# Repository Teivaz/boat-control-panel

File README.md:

# Panel 01

Electrical control panel for a boat. A single three-board unit that drives the
cabin relays, exposes them through a button panel with per-button RGB
feedback, and displays system state (battery, fuel and fresh-water level,
sensors, clock, nav-light selection) on a small OLED.

## Hardware layout

Three PIC18F27Q84 boards communicate over a shared I2C bus (multi-master):

| Board | Directory | Role |
|---|---|---|
| Switching | `circuit/board1-switching/` | 16 relay outputs (shift-register + mux back-read), 2 float-meter inputs, battery divider, 3 digital sensors (bilge / shore / AC). |
| Button (L/R) | `circuit/board2-buttons/` | 7 momentary buttons with per-button RGB indicator LEDs and configurable trigger modes. Two physical boards per unit (left and right), address selected by strap. |
| Main | `circuit/board3-main/` | SSD1322 OLED, DS3231 RTC, config switch. Orchestrates the other boards: receives button events, maintains relay intent, drives nav-light logic, and hosts the config menu. |

## Repository layout

- `firmware/` — C firmware for all three boards. Self-contained build via
  Docker (`firmware/build.sh`). See [`firmware/CLAUDE.md`](firmware/CLAUDE.md)
  and [`firmware/protocol.md`](firmware/protocol.md) for the I2C protocol,
  module conventions, and per-board details.
- `circuit/` — KiCad schematics and PCB layouts, one directory per board plus
  a shared symbol/footprint library (`panel-library.*`) and connection
  diagrams.
- `design/` — Front-panel artwork (Affinity Designer / Photo sources) and DXF
  exports for panel cutouts.
- `models/` — STEP files for mechanical assemblies and 3D-printed parts.
- `playground/` — Experimental sketches (currently the SSD1322 I2C display
  bring-up).

## Functional overview

- **Power**: a panel-wide power button on the left board gates every
  non-nav-light relay. Relay and nav-mode state are restored from a RAM
  snapshot when power is toggled back on.
- **Relays (5..15)**: instruments, autopilot, inverter, water pump, fridge,
  deck/cabin lights, USB, two aux channels. Each is tied to a single button
  and toggles on press. A button flags ERROR when the physical relay state
  doesn't converge to the requested one.
- **Nav lights (relays 0..4)**: anchoring / tricolor / steaming / bow / stern
  driven by a 3-button nav-mode selector. The main board filters requested
  combinations against the configured "enabled lights" mask (set in the
  config menu) and surfaces an error if the request is incompatible.
- **Config mode**: toggling the RA7 switch on the main board enters a menu
  (nav-light mask, time-of-day, water/fuel float offsets). The same buttons
  become menu navigation while active.
- **Button trigger modes**: each button has an independent trigger
  (release / hold / change) and time threshold, configured via the protocol
  and persisted to each board's data EEPROM.

## Firmware highlights

- No RTOS — all boards share a cooperative 1 ms-tick scheduler (`libcomm/
  task.c`) with a deferred ISR-to-main-loop queue (`run_in_main_loop`).
- Transport-agnostic protocol library (`libcomm/`) linked into all three
  boards. I2C, buttons, relays, NVM, and display code are board-local.
- Built with Microchip XC8 v3.10 inside a pinned Docker image; no MPLAB X
  install required. `./firmware/build.sh` from a board source directory
  produces a `.hex` in `dist/default/production/`.
- No unit tests — validation is done on hardware via a PICkit/ICD
  programmer. Per-board readmes in `firmware/board{1,3}/readme.md` document
  pinout and wiring.

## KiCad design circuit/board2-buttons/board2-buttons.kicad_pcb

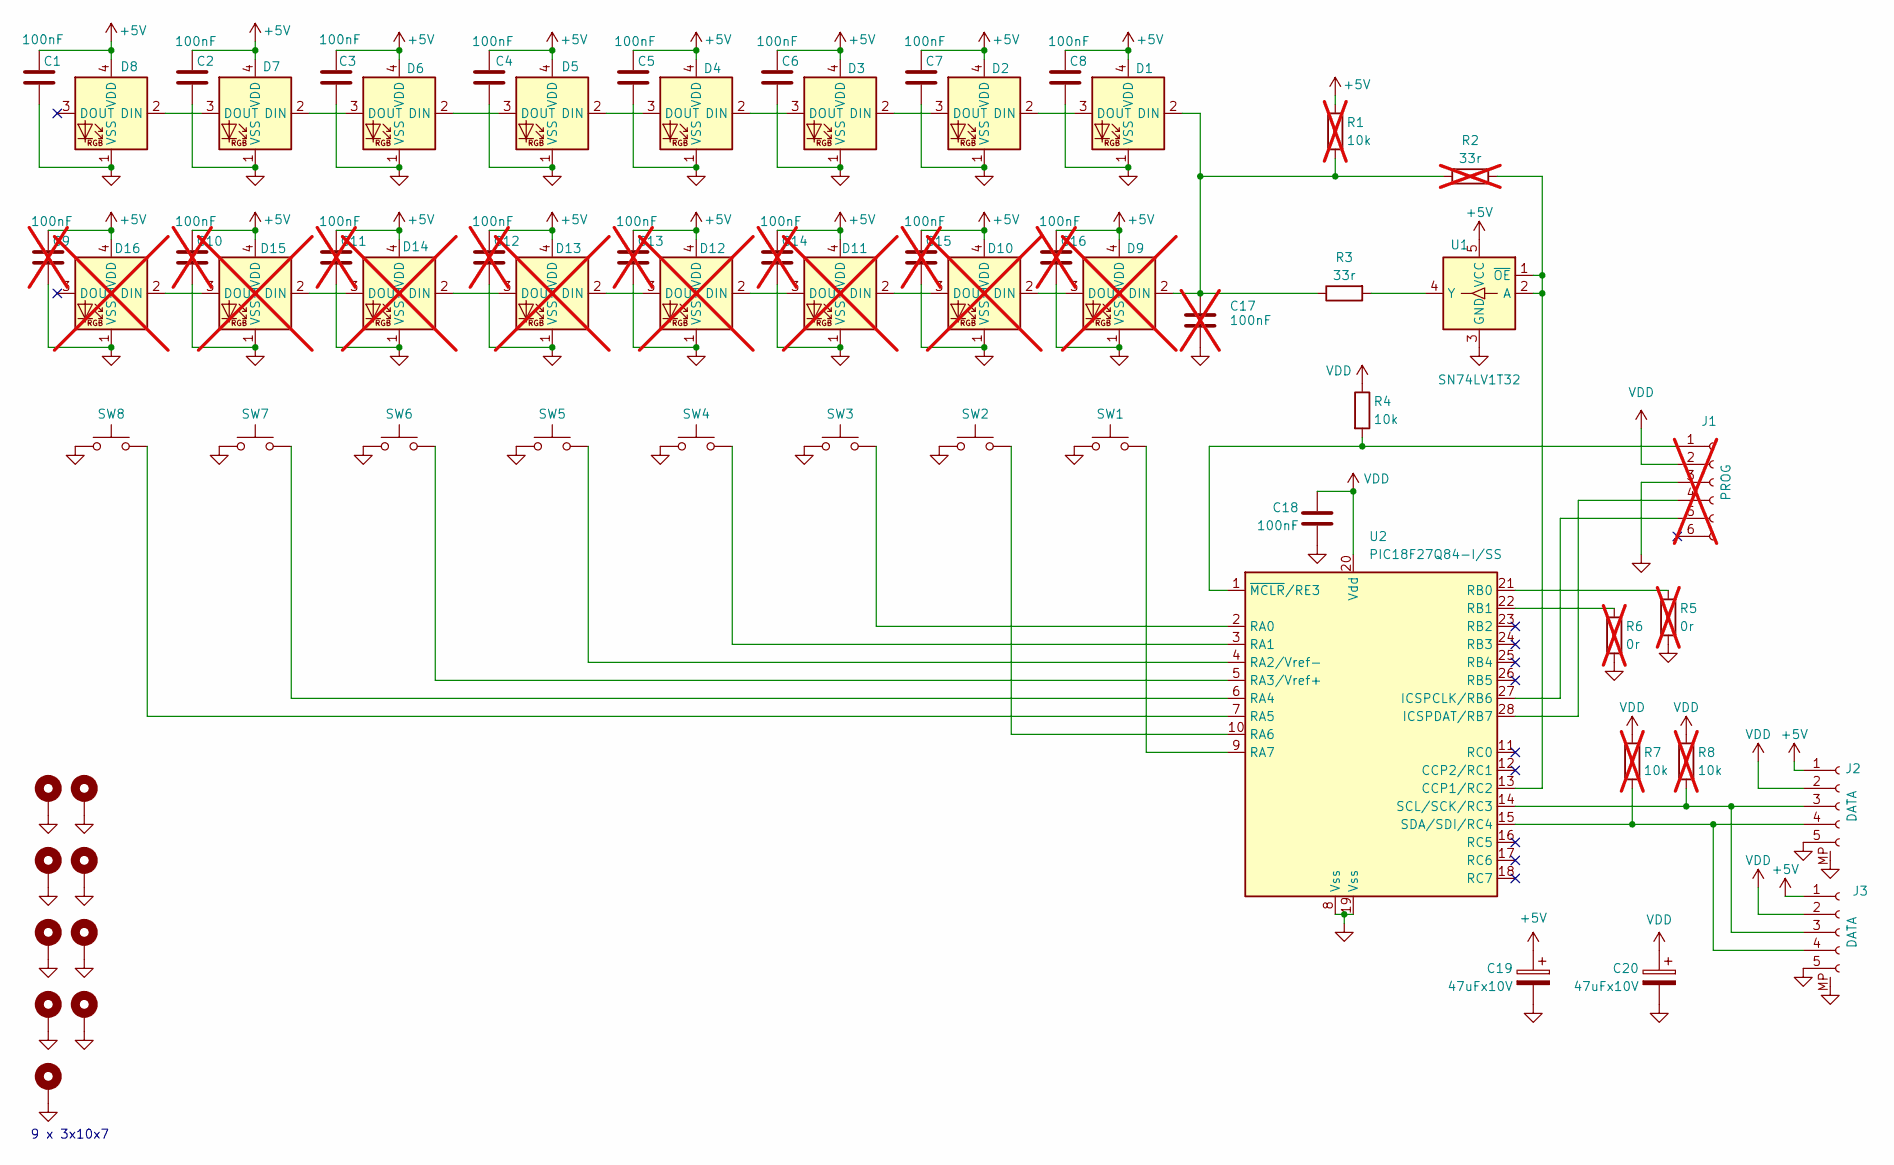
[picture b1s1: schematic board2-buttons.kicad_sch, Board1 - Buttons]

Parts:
C1, C2, C3, C4, C5, C6, C7, C8, C18: 100nF; C_0805_2012Metric_Pad1.18x1.45mm_HandSolder
C9, C10, C11, C12, C13, C14, C15, C16, C17: 100nF; C_0805_2012Metric_Pad1.18x1.45mm_HandSolder; not fitted
C19, C20: 47uFx10V; CP_EIA-3528-12_Kemet-T_HandSolder
D1, D2, D3, D4, D5, D6, D7, D8: LiteOn_LTST-E563C; LED_LiteOn_LTST-E563C_PLCC4_5.0x5.0mm_P3.2mm
D9, D10, D11, D12, D13, D14, D15, D16: LiteOn_LTST-E563C; LED_LiteOn_LTST-E563C_PLCC4_5.0x5.0mm_P3.2mm; not fitted
H1, H2, H3, H4, H5, H6, H7, H8, H9: 3X10X7; MountingHole_3.2mm_M3_Pad_Via_oval
J1: 1x5x2.54; PinHeader_1x06_P2.54mm_Vertical; not fitted
J2, J3: PicoLock; Molex_Pico-Lock_504050-0591_1x05-1MP_P1.50mm_Horizontal
R1, R7, R8: 10k; R_0805_2012Metric_Pad1.20x1.40mm_HandSolder; not fitted
R2: 33r; R_0805_2012Metric_Pad1.20x1.40mm_HandSolder; not fitted
R3: 33r; R_0805_2012Metric_Pad1.20x1.40mm_HandSolder
R4: 10k; R_0805_2012Metric_Pad1.20x1.40mm_HandSolder
R5, R6: 0r; R_0805_2012Metric_Pad1.20x1.40mm_HandSolder; not fitted
SW1, SW2, SW3, SW4, SW5, SW6, SW7, SW8: EVPCD; ButtonSMT_Panasonic_EVPCD
U1: SN74LV1T32; SOT-23-5
U2: PIC18F27Q84-I/SS; SSOP-28-5.3mm

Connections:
+5V: C1.1, C2.1, C3.1, C4.1, C5.1, C6.1, C7.1, C8.1, C9.1, C10.1, C11.1, C12.1, C13.1, C14.1, C15.1, C16.1, C19.1, D1.4 (VDD), D2.4 (VDD), D3.4 (VDD), D4.4 (VDD), D5.4 (VDD), D6.4 (VDD), D7.4 (VDD), D8.4 (VDD), D9.4 (VDD), D10.4 (VDD), D11.4 (VDD), D12.4 (VDD), D13.4 (VDD), D14.4 (VDD), D15.4 (VDD), D16.4 (VDD), J2.1, J3.1, R1.1, U1.5 (VCC)
GND: C1.2, C2.2, C3.2, C4.2, C5.2, C6.2, C7.2, C8.2, C9.2, C10.2, C11.2, C12.2, C13.2, C14.2, C15.2, C16.2, C17.1, C18.2, C19.2, C20.2, D1.1 (VSS), D2.1 (VSS), D3.1 (VSS), D4.1 (VSS), D5.1 (VSS), D6.1 (VSS), D7.1 (VSS), D8.1 (VSS), D9.1 (VSS), D10.1 (VSS), D11.1 (VSS), D12.1 (VSS), D13.1 (VSS), D14.1 (VSS), D15.1 (VSS), D16.1 (VSS), H1.1, H2.1, H3.1, H4.1, H5.1, H6.1, H7.1, H8.1, H9.1, J1.3, J2.5, J2.MP, J3.5, J3.MP, R5.1, R6.2, SW1.1, SW2.1, SW3.1, SW4.1, SW5.1, SW6.1, SW7.1, SW8.1, U1.3 (GND), U2.8 (Vss), U2.19 (Vss)
unnamed: C17.2, D1.2 (DIN), D9.2 (DIN), R1.2, R2.2, R3.1
unnamed: D1.3 (DOUT), D2.2 (DIN)
unnamed: D2.3 (DOUT), D3.2 (DIN)
unnamed: D3.3 (DOUT), D4.2 (DIN)
unnamed: D4.3 (DOUT), D5.2 (DIN)
unnamed: D5.3 (DOUT), D6.2 (DIN)
unnamed: D6.3 (DOUT), D7.2 (DIN)
unnamed: D7.3 (DOUT), D8.2 (DIN)
unnamed: D9.3 (DOUT), D10.2 (DIN)
unnamed: D10.3 (DOUT), D11.2 (DIN)
unnamed: D11.3 (DOUT), D12.2 (DIN)
unnamed: D12.3 (DOUT), D13.2 (DIN)
unnamed: D13.3 (DOUT), D14.2 (DIN)
unnamed: D14.3 (DOUT), D15.2 (DIN)
unnamed: D15.3 (DOUT), D16.2 (DIN)
unnamed: J1.1, R4.2, U2.1 (~MCLR/RE3)
unnamed: J1.4, U2.28 (ICSPDAT/RB7)
unnamed: J1.5, U2.27 (ICSPCLK/RB6)
unnamed: J2.3, J3.3, R8.2, U2.14 (SCL/SCK/RC3)
unnamed: J2.4, J3.4, R7.2, U2.15 (SDA/SDI/RC4)
unnamed: R2.1, U1.1 (~OE), U1.2 (A), U2.13 (CCP1/RC2)
unnamed: R3.2, U1.4 (Y)
unnamed: SW3.2, U2.2 (RA0)
unnamed: SW4.2, U2.3 (RA1)
unnamed: SW5.2, U2.4 (RA2/Vref-)
unnamed: SW6.2, U2.5 (RA3/Vref+)
unnamed: SW7.2, U2.6 (RA4)
unnamed: SW8.2, U2.7 (RA5)
unnamed: SW2.2, U2.10 (RA6)
unnamed: SW1.2, U2.9 (RA7)
unnamed: R5.2, U2.21 (RB0)
unnamed: R6.1, U2.22 (RB1)
VDD: C18.1, C20.1, J1.2, J2.2, J3.2, R4.1, R7.1, R8.1, U2.20 (Vdd)

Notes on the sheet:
9 x 3x10x7

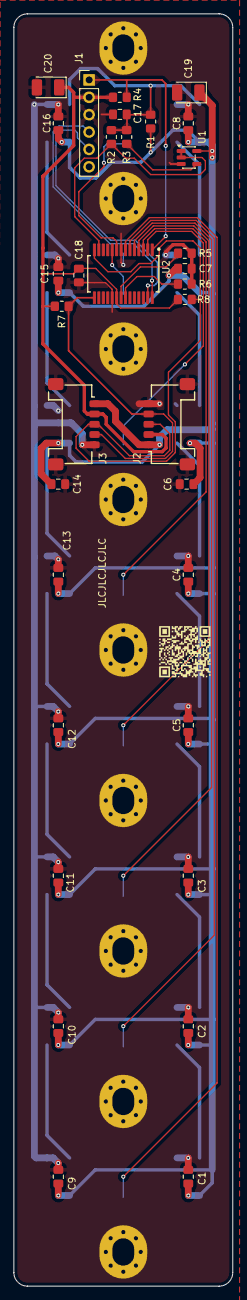
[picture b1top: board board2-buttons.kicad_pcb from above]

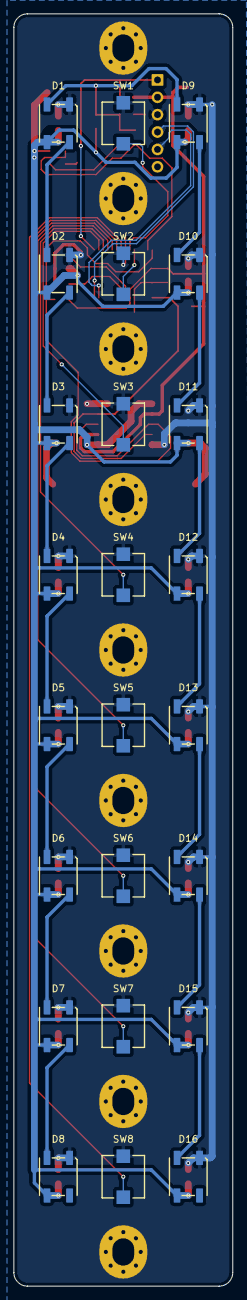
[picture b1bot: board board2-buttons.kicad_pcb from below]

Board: 2 copper layers, 32.0 x 186.0 mm, 66 parts (24 on the bottom side), 35 nets.

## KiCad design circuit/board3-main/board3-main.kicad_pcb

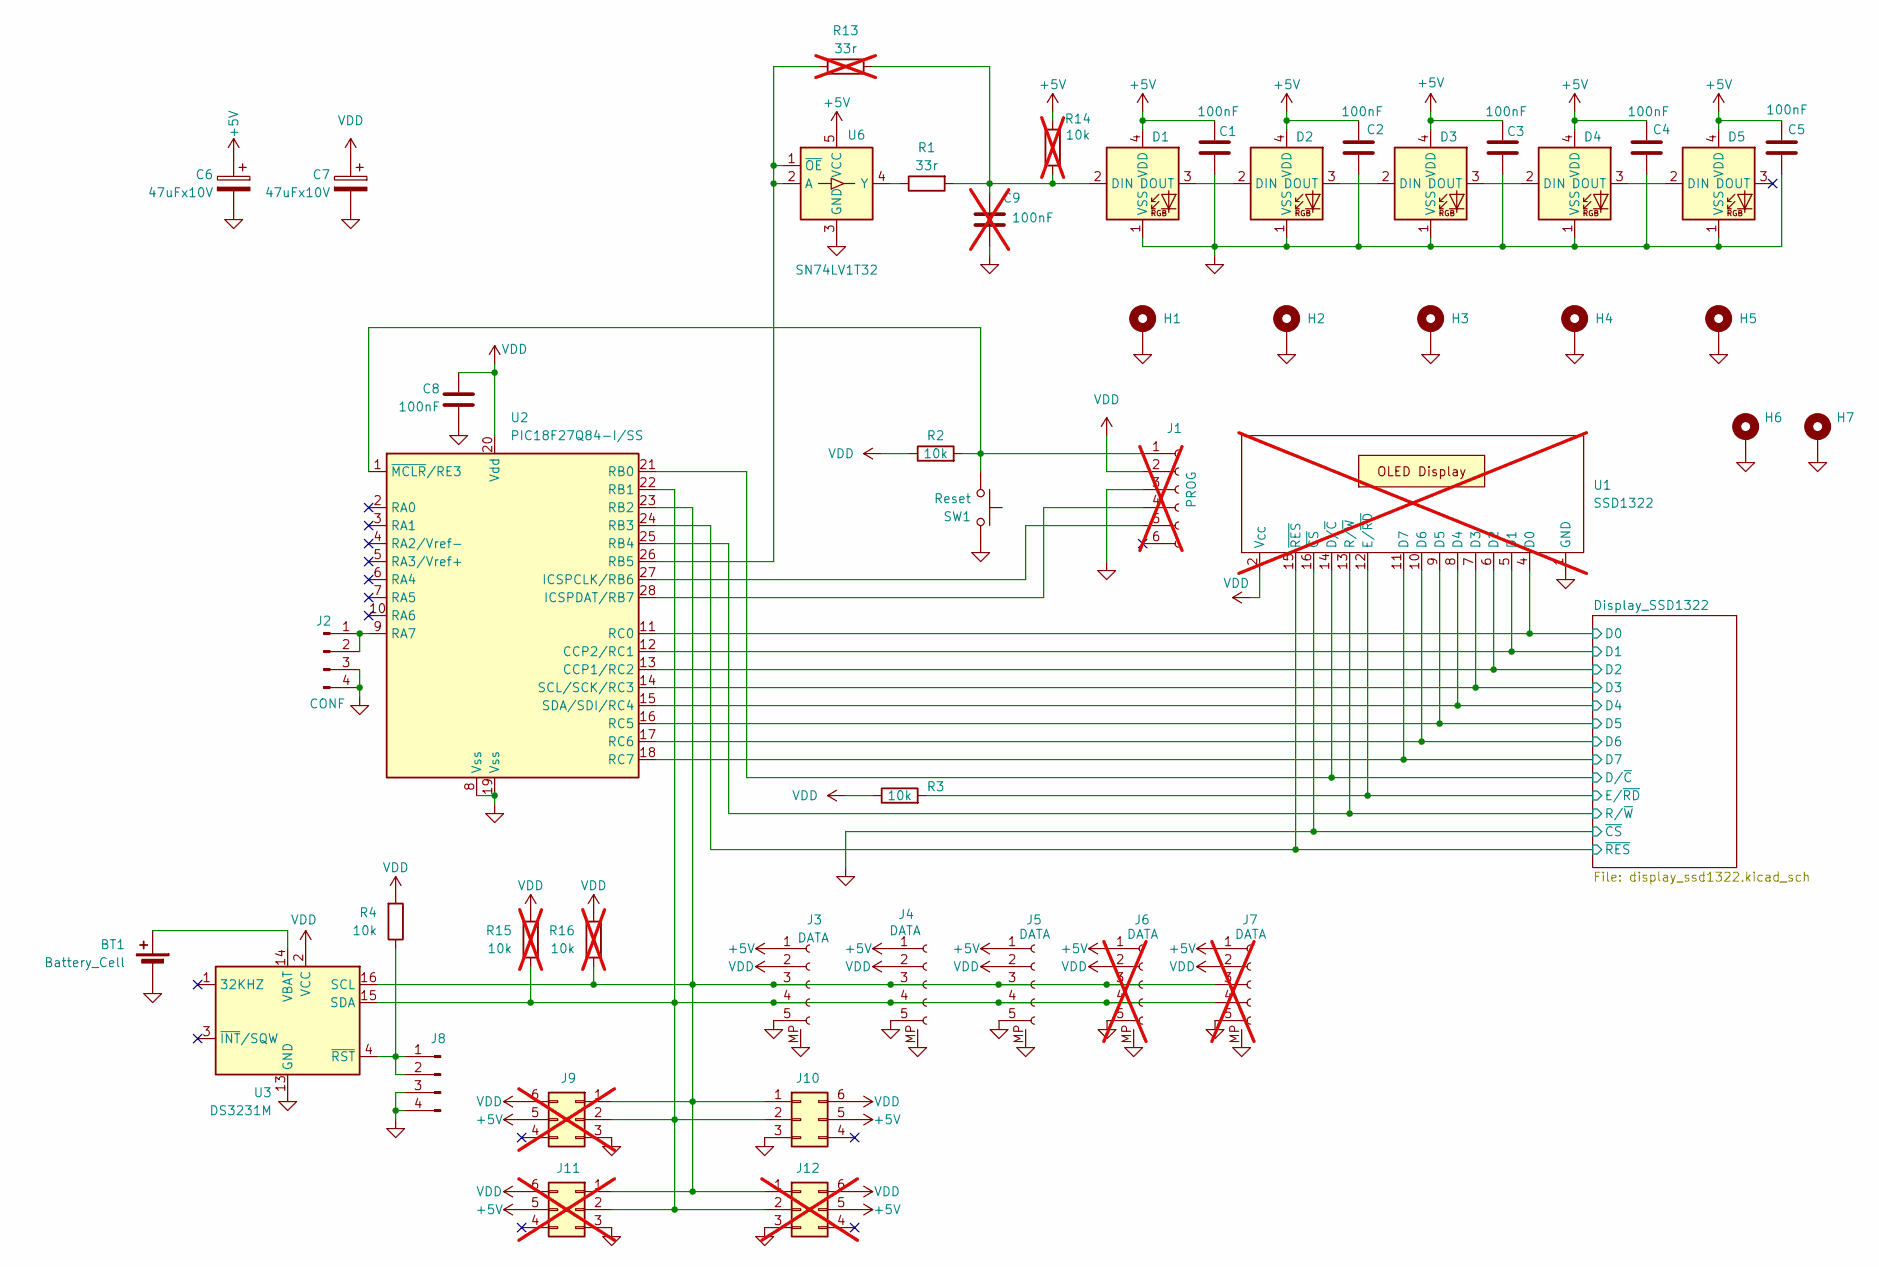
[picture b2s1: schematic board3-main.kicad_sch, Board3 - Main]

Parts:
BT1: Battery_Cell; Bat_Keystone_1058
C1, C2, C3, C4, C5, C8: 100nF; C_0805_2012Metric_Pad1.18x1.45mm_HandSolder
C6, C7: 47uFx10V; CP_EIA-3528-21_Kemet-B_HandSolder
C9: 100nF; C_0805_2012Metric_Pad1.18x1.45mm_HandSolder; not fitted
D1, D2, D3, D4, D5: LiteOn_LTST-E563C; LED_LiteOn_LTST-E563C_PLCC4_5.0x5.0mm_P3.2mm_MIN
H1, H2, H3, H4, H5: MountingHole_Pad; ledpipe_5x5
H6, H7: MountingHole_Pad; MountingHole_3.2mm_M3_Pad_Via
J1: PinHeader_1x06_P2.54mm_Vertical; not fitted
J2: CONF; PinHeader_1x04_P2.00mm_Vertical_SMD_Pin1Left
J3, J4, J5: Molex_Pico-Lock_504050-0591_1x05-1MP_P1.50mm_Horizontal
J6, J7: Molex_Pico-Lock_504050-0591_1x05-1MP_P1.50mm_Horizontal; not fitted
J8: PinHeader_1x04_P2.00mm_Vertical_SMD_Pin1Left
J9, J11, J12: Conn_02x03_Counter_Clockwise; Con-Amphenol-76385-303LF; not fitted
J10: Conn_02x03_Counter_Clockwise; Con-Amphenol-76385-303LF
R1: 33r; R_0805_2012Metric_Pad1.20x1.40mm_HandSolder
R2, R3, R4: 10k; R_0805_2012Metric_Pad1.20x1.40mm_HandSolder
R13: 33r; R_0805_2012Metric_Pad1.20x1.40mm_HandSolder; not fitted
R14, R15, R16: 10k; R_0805_2012Metric_Pad1.20x1.40mm_HandSolder; not fitted
SW1: Reset; ButtonSMT_CnK_KSC2_J
U1: SSD1322; Display_256x64_3.12in_board; not fitted
U2: PIC18F27Q84-I/SS; SSOP-28-5.3mm
U3: DS3231M; SOIC-16W_7.5x10.3mm_P1.27mm
U6: SN74LV1T32; SOT-23-5

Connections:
+5V: C1.1, C2.1, C3.1, C4.1, C5.1, C6.1, D1.4 (VDD), D2.4 (VDD), D3.4 (VDD), D4.4 (VDD), D5.4 (VDD), J3.1, J4.1, J5.1, J6.1, J7.1, J9.5, J10.5, J11.5, J12.5, R14.2, U6.5 (VCC); also elsewhere on the board
/Display_SSD1322/D0: U1.4 (D0), U2.11 (RC0); also elsewhere on the board
/Display_SSD1322/D1: U1.5 (D1), U2.12 (CCP2/RC1); also elsewhere on the board
/Display_SSD1322/D2: U1.6 (D2), U2.13 (CCP1/RC2); also elsewhere on the board
/Display_SSD1322/D3: U1.7 (D3), U2.14 (SCL/SCK/RC3); also elsewhere on the board
/Display_SSD1322/D4: U1.8 (D4), U2.15 (SDA/SDI/RC4); also elsewhere on the board
/Display_SSD1322/D5: U1.9 (D5), U2.16 (RC5); also elsewhere on the board
/Display_SSD1322/D6: U1.10 (D6), U2.17 (RC6); also elsewhere on the board
/Display_SSD1322/D7: U1.11 (D7), U2.18 (RC7); also elsewhere on the board
/Display_SSD1322/D/~C: U1.14 (D/~C), U2.21 (RB0); also elsewhere on the board
/Display_SSD1322/E/~RD: R3.2, U1.12 (E/~RD); also elsewhere on the board
/Display_SSD1322/R/~W: U1.13 (R/~W), U2.25 (RB4); also elsewhere on the board
/Display_SSD1322/~RES: U1.15 (~RES), U2.24 (RB3); also elsewhere on the board
GND: BT1.2 (-), C1.2, C2.2, C3.2, C4.2, C5.2, C6.2, C7.2, C8.2, C9.1, D1.1 (VSS), D2.1 (VSS), D3.1 (VSS), D4.1 (VSS), D5.1 (VSS), H1.1, H2.1, H3.1, H4.1, H5.1, H6.1, H7.1, J1.3, J2.3, J2.4, J3.5, J3.MP, J4.5, J4.MP, J5.5, J5.MP, J6.5, J6.MP, J7.5, J7.MP, J8.3, J8.4, J9.3, J10.3, J11.3, J12.3, SW1.2, SW1.4, U1.1 (GND), U1.16 (~CS), U2.8 (Vss), U2.19 (Vss), U3.5 (GND), U3.6 (GND), U3.7 (GND), U3.8 (GND), U3.9 (GND), U3.10 (GND), U3.11 (GND), U3.12 (GND), U3.13 (GND), U6.3 (GND); also elsewhere on the board
unnamed: BT1.1 (+), U3.14 (VBAT)
unnamed: C9.2, D1.2 (DIN), R1.2, R13.2, R14.1
unnamed: D1.3 (DOUT), D2.2 (DIN)
unnamed: D2.3 (DOUT), D3.2 (DIN)
unnamed: D3.3 (DOUT), D4.2 (DIN)
unnamed: D4.3 (DOUT), D5.2 (DIN)
unnamed: J1.1, R2.2, SW1.1, SW1.3, U2.1 (~MCLR/RE3)
unnamed: J1.4, U2.28 (ICSPDAT/RB7)
unnamed: J1.5, U2.27 (ICSPCLK/RB6)
unnamed: J2.1, J2.2, U2.9 (RA7)
unnamed: J8.1, J8.2, R4.1, U3.4 (~RST)
unnamed: J3.3, J4.3, J5.3, J6.3, J7.3, J9.1, J10.1, J11.1, J12.1, R16.1, U2.23 (RB2), U3.16 (SCL)
unnamed: J3.4, J4.4, J5.4, J6.4, J7.4, J9.2, J10.2, J11.2, J12.2, R15.1, U2.22 (RB1), U3.15 (SDA)
unnamed: R13.1, U2.26 (RB5), U6.1 (~OE), U6.2 (A)
unnamed: R1.1, U6.4 (Y)
VDD: C7.1, C8.1, J1.2, J3.2, J4.2, J5.2, J6.2, J7.2, J9.6, J10.6, J11.6, J12.6, R2.1, R3.1, R4.2, R15.2, R16.2, U1.2 (V_{CC}), U2.20 (Vdd), U3.2 (VCC); also elsewhere on the board

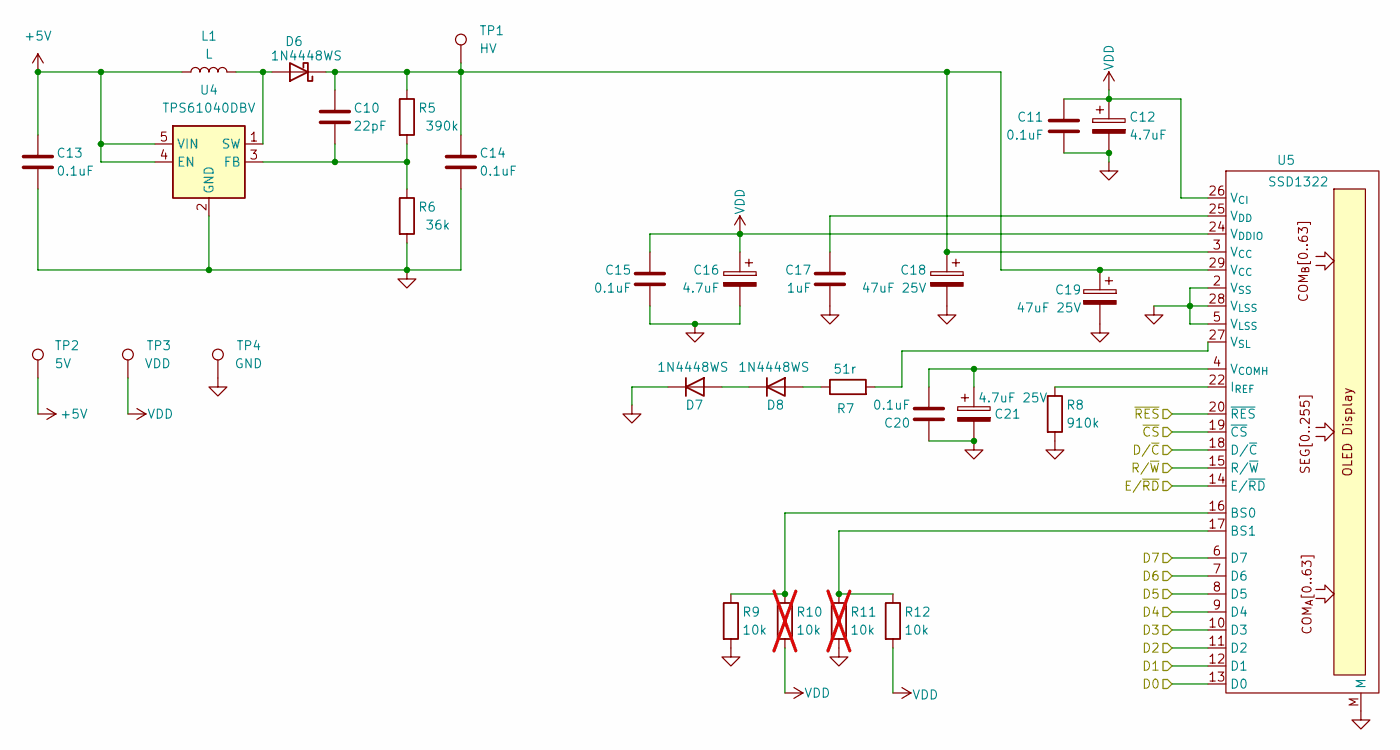
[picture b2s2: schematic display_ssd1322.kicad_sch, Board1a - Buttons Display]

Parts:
C10: 22pF; C_0805_2012Metric_Pad1.18x1.45mm_HandSolder
C11, C13, C15: 0.1uF; C_0805_2012Metric_Pad1.18x1.45mm_HandSolder
C12, C16: 4.7uF; CP_EIA-3528-12_Kemet-T_HandSolder
C14, C20: 0.1uF; C_0603_1608Metric_Pad1.08x0.95mm_HandSolder
C17: 1uF; C_0603_1608Metric_Pad1.08x0.95mm_HandSolder
C18, C19: 47uF 25V; CP_EIA-7343-31_Kemet-D_HandSolder
C21: 4.7uF 25V; CP_EIA-3216-18_Kemet-A_HandSolder
D6, D7, D8: 1N4448WS; D_SOD-323_HandSoldering
L1: L; L_Abracon_ASPI-3012S
R5: 390k; R_0805_2012Metric_Pad1.20x1.40mm_HandSolder
R6: 36k; R_0805_2012Metric_Pad1.20x1.40mm_HandSolder
R7: 51r; R_0805_2012Metric_Pad1.20x1.40mm_HandSolder
R8: 910k; R_0805_2012Metric_Pad1.20x1.40mm_HandSolder
R9, R12: 10k; R_0805_2012Metric_Pad1.20x1.40mm_HandSolder
R10, R11: 10k; R_0805_2012Metric_Pad1.20x1.40mm_HandSolder; not fitted
TP1: HV; TestPoint_Pad_D2.0mm
TP2: 5V; TestPoint_Pad_D2.0mm
TP3: VDD; TestPoint_Pad_D2.0mm
TP4: GND; TestPoint_Pad_D2.0mm
U4: TPS61040DBV; SOT-23-5
U5: SSD1322; Display_256x64_3.12in_flip

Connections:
+5V: C13.1, L1.1, TP2.1, U4.4 (EN), U4.5 (VIN); also elsewhere on the board
/Display_SSD1322/D0: U5.13 (D0); also elsewhere on the board
/Display_SSD1322/D1: U5.12 (D1); also elsewhere on the board
/Display_SSD1322/D2: U5.11 (D2); also elsewhere on the board
/Display_SSD1322/D3: U5.10 (D3); also elsewhere on the board
/Display_SSD1322/D4: U5.9 (D4); also elsewhere on the board
/Display_SSD1322/D5: U5.8 (D5); also elsewhere on the board
/Display_SSD1322/D6: U5.7 (D6); also elsewhere on the board
/Display_SSD1322/D7: U5.6 (D7); also elsewhere on the board
/Display_SSD1322/D/~C: U5.18 (D/~C); also elsewhere on the board
/Display_SSD1322/E/~RD: U5.14 (E/~RD); also elsewhere on the board
/Display_SSD1322/R/~W: U5.15 (R/~W); also elsewhere on the board
/Display_SSD1322/~RES: U5.20 (~RES); also elsewhere on the board
GND: C11.2, C12.2, C13.2, C14.2, C15.2, C16.2, C17.2, C18.2, C19.2, C20.1, C21.2, D7.1 (K), R6.2, R8.2, R9.2, R11.2, TP4.1, U4.2 (GND), U5.2 (V_{SS}), U5.5 (V_{LSS}), U5.19 (~CS), U5.28 (V_{LSS}), U5.M; also elsewhere on the board
unnamed: D6.2 (A), L1.2, U4.1 (SW)
unnamed: C10.1, C14.1, C18.1, C19.1, D6.1 (K), R5.1, TP1.1, U5.3 (V_{CC}), U5.29 (V_{CC})
unnamed: D7.2 (A), D8.1 (K)
unnamed: D8.2 (A), R7.1
unnamed: C10.2, R5.2, R6.1, U4.3 (FB)
unnamed: R9.1, R10.1, U5.16 (BS0)
unnamed: R11.1, R12.1, U5.17 (BS1)
unnamed: R8.1, U5.22 (I_{REF})
unnamed: C20.2, C21.1, U5.4 (V_{COMH})
unnamed: C17.1, U5.25 (V_{DD})
unnamed: R7.2, U5.27 (V_{SL})
VDD: C11.1, C12.1, C15.1, C16.1, R10.2, R12.2, TP3.1, U5.24 (V_{DDIO}), U5.26 (V_{CI}); also elsewhere on the board

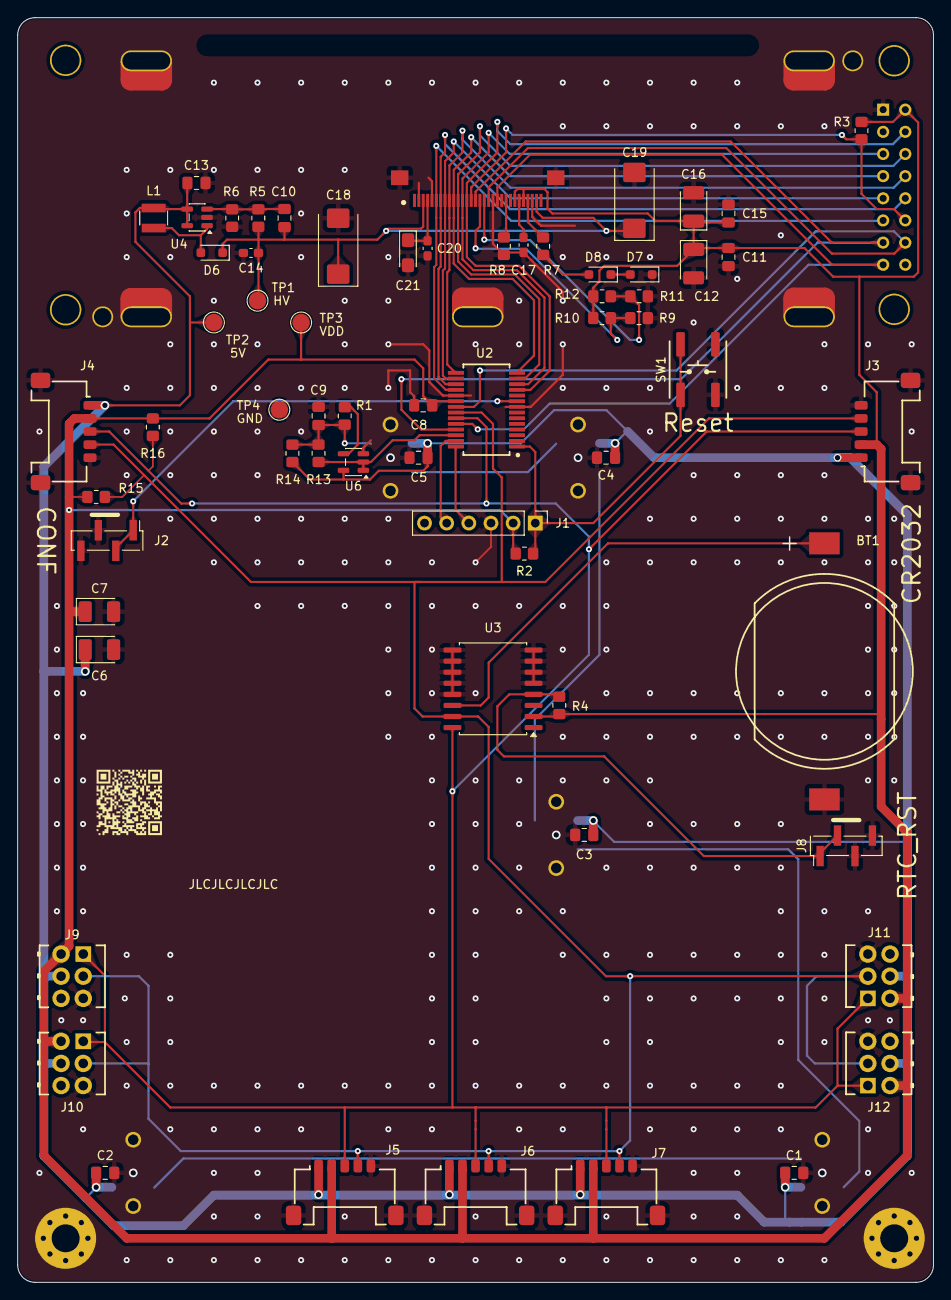
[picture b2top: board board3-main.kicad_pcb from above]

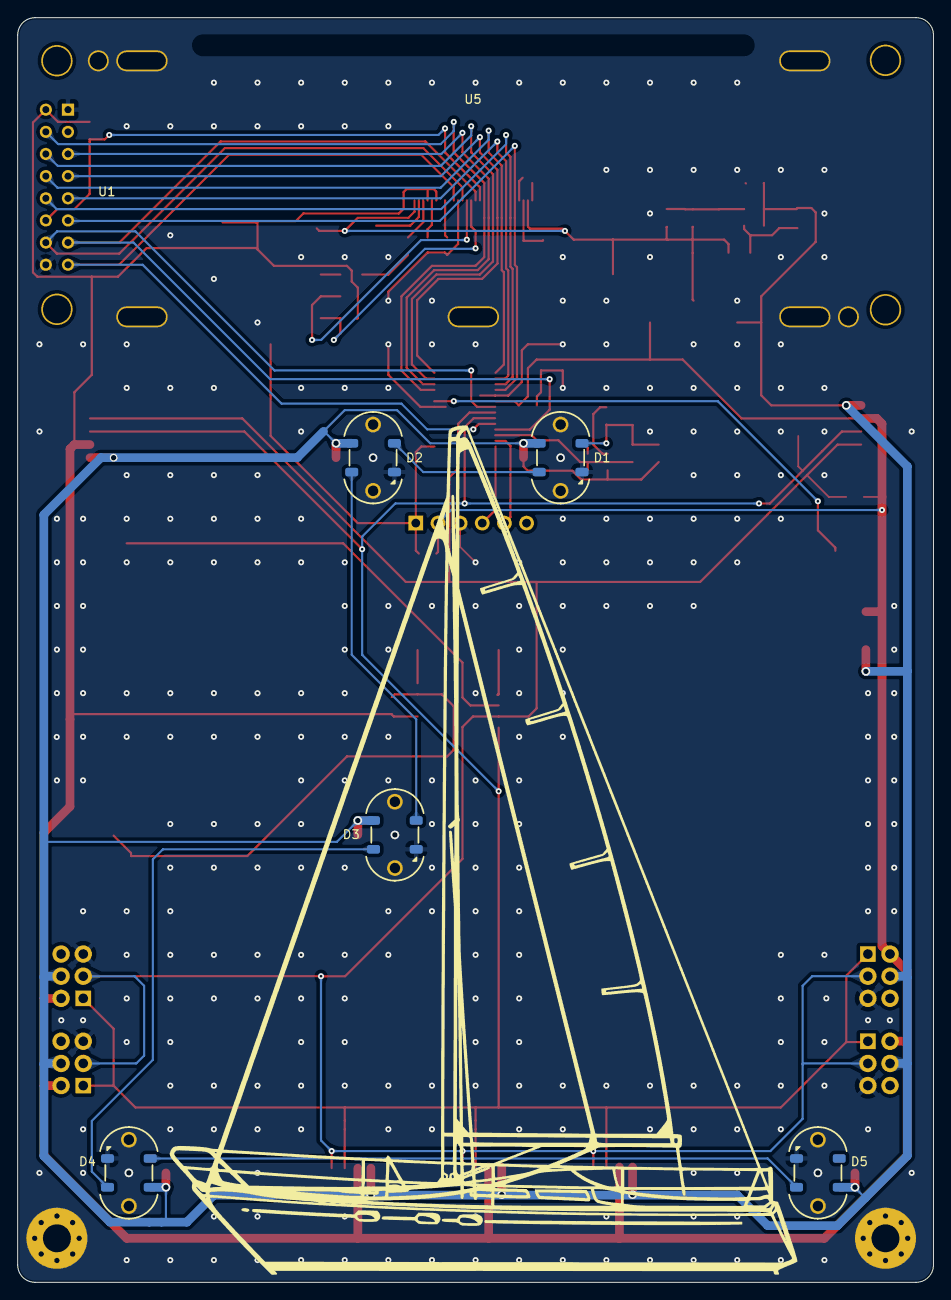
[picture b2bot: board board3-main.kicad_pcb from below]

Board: 2 copper layers, 105.0 x 145.0 mm, 77 parts (12 on the bottom side), 41 nets.
